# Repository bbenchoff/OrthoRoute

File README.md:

<table width="100%">
  <tr>
    <td align="center" width="300">
      
    </td>
    <td align="left">
      <h2>OrthoRoute - GPU Accelerated Autorouting for KiCad</h2>
      <p><strong>OrthoRoute is a GPU-accelerated PCB autorouter designed specifically for a narrow class of extremely large, dense, highly regular multilayer backplanes and BGA escape patterns. It uses a Manhattan lattice and the PathFinder algorithm to route designs with thousands of nets. It is not a general-purpose PCB autorouter.</strong></p>
      <p><em>Orthogonal! Non-trivial! Runs on GPUs! I live in San Francisco!</em></p>
      <p><em>Never trust the autorouter, but at least this one is fast. </em></p>
    </td>
  </tr>
</table>

> [!CAUTION]
> **OrthoRoute is not a general-purpose PCB autorouter.**
>
> OrthoRoute is designed for a narrow class of extremely large, dense, highly
> regular multilayer backplanes and BGA escape patterns. It is useful to about
> five people on the planet, and you probably aren't one of them. For a 
> conventional PCB, use something else.
>
> In *[PCBWorld: A Benchmark Environment for Engine-Grounded PCB Design
> Automation](https://arxiv.org/abs/2607.05915)*, Song et al. benchmarked
> OrthoRoute against Freerouting, KiCadRoutingTools, and several learned routing
> agents on synthetic and open-source PCB datasets.[^pcbworld]
>
> * On the synthetic D2 dataset, OrthoRoute achieved a **1% clean-pass rate**
>   and **30% routability**.
> * On D3-A, a set of 99 open-source boards, it achieved a **2% clean-pass
>   rate** and **51% routability**.
> * Freerouting and KiCadRoutingTools performed dramatically better on both
>   datasets.
>
> The benchmark used small, ordinary boards and OrthoRoute's upstream defaults;
> it did not test OrthoRoute's intended thousands-net backplane workload. It
> nevertheless demonstrates that OrthoRoute is a terrible default choice for
> ordinary PCB autorouting.

[^pcbworld]: Hyungseok Song et al., “[PCBWorld: A Benchmark Environment for
Engine-Grounded PCB Design Automation](https://arxiv.org/abs/2607.05915),”
*arXiv preprint* arXiv:2607.05915, 2026, Table 3 and Appendix K.5.

A much more comprehensive explanation of the _WHY_ and _HOW_ of this repository is available on the [build log for this project](https://bbenchoff.github.io/pages/OrthoRoute.html).

## Videos

<table>
  <tr>
    <td align="center" width="33%">
      <a href="https://www.youtube.com/watch?v=KXxxNQPTagA">
        
        <br/>
        <b>OrthoRoute Overview</b>
      </a>
    </td>
    <td align="center" width="33%">
      <a href="https://www.youtube.com/watch?v=P8Wsej71XAQ">
        
        <br/>
        <b>Algorithm Demonstration</b>
      </a>
    </td>
    <td align="center" width="33%">
      <a href="https://www.youtube.com/watch?v=j_XJNxEXXkQ">
        
        <br/>
        <b>PathFinder Net Tour</b>
      </a>
    </td>
  </tr>
</table>

## What Is Orthoroute?

OrthoRoute is a KiCad autorouter for _exceptionally large_ or _very complex_ backplane designs and BGA escape patterns. The simplified idea behind this algorithm is, "put all your parts on the top layer, and on layers below that, create a grid of traces. Only horizontal traces on layer 1, only vertical traces on layer 2, and continue like that for all the other layers. Route through this 'Manhattan grid' of traces with blind and buried vias".

The algorithm used for this autorouter is [PathFinder: a negotiation-based performance-driven router for FPGAs](https://dl.acm.org/doi/10.1145/201310.201328). My implementation of PathFinder treats the PCB as a graph: nodes are intersections on an x–y grid where vias can go, and edges are the segments between intersections where copper traces can run. Each edge and node is treated as a shared resource.

PathFinder is iterative. In the first iteration, all nets (airwires) are routed _greedily_, without accounting for overuse of nodes or edges. Subsequent iterations account for congestion, increasing the “cost” of overused edges and ripping up the worst offenders to re-route them. Over time, the algorithm _converges_ to a PCB layout where no edge or node is over-subscribed by multiple nets.

With this architecture -- the PathFinder algorithm on a very large graph, within the same order of magnitude of the largest FPGAs -- it makes sense to run the algorithm with GPU acceleration. There are a few factors that went into this decision:

1. Everyone who's routing giant backplanes probably has a gaming PC. Or you can rent a GPU from whatever company is advertising on MUNI bus stops this month.
2. The PathFinder algorithm requires hundreds of billions of calculations for every iteration, making single-core CPU computation glacially slow. 
3. With CUDA, I can implement a SSSP (parallel Dijkstra) to find a path through a weighted graph very fast. 

Note this is _not_ a fully parallel autorouter; in OrthoRoute, nets are still routed in sequence on a shared congestion map. The parallelism lives inside the shortest-path search: a CUDA SSSP (“parallel Dijkstra”) kernel makes each individual net’s pathfinding fast, but it doesn’t route many nets simultaneously.

## Features

- KiCad Integration: Built as a native KiCad plugin using the IPC API
- GPU-Accelerated Routing: Uses CUDA/CuPy or Apple Silicon/Metal
- Manhattan Routing: Specialized for orthogonal routing patterns (horizontal/vertical layer pairs)
- Real-time Visualization: Interactive 2D board view with zoom, pan, and layer controls
- Checkpoint system for instant resume after crashes (experimental)
- Headless (Cloud) Routing: Rent an A100 GPU in some datacenter

## Screenshots

### Main Interface

<div align="center">
  
  <br>
  <em>OrthoRoute plugin showing a successful Manhattan route</em>
</div>

<div align="center">
  
  <br>
  <em>A view of what the 'Manhattan Lattice' looks like in KiCad</em>
</div>

<div align="center">
  
  <br>
  <em>OrthoRoute plugin showing a successful Manhattan route</em>
</div>

## Quick Start

### Prerequisites
- **KiCad 10.0+** with the API server enabled under Preferences → Plugins
- An NVIDIA CUDA 12 GPU on Windows/Linux, or Apple Silicon on macOS
- Enough accelerator memory for the board and routing grid

### Installation Methods

#### Install the KiCad package

1. Download
   [`OrthoRoute-1.0.0-KiCad-PCM.zip`](https://github.com/bbenchoff/OrthoRoute/releases/download/v1.0.0/OrthoRoute-1.0.0-KiCad-PCM.zip),
   or build it from source using the instructions below.
2. In KiCad 10, open **Plugin and Content Manager** and choose
   **Install from File...**.
3. Select the OrthoRoute PCM ZIP.
4. Enable the API server under **Preferences > Plugins**.
5. Restart PCB Editor and allow several minutes for KiCad to create
   OrthoRoute's isolated Python environment and install its dependencies.
6. Open a board and launch **OrthoRoute** from
   **Tools > External Plugins**.

#### Build the package from source

Clone the repository and run the package builder:

```bash
git clone https://github.com/bbenchoff/OrthoRoute.git
cd OrthoRoute
python build.py
```

The builder creates:

- `build/OrthoRoute-1.0.0-KiCad-PCM.zip` for KiCad 10's
  **Install from File...** command
- `build/OrthoRoute-1.0.0-KiCad-IPC.zip` for manual native-plugin installation

Developers can build and deploy directly into their newest local KiCad
installation:

```bash
python build.py --deploy
```

Use `python build.py --deploy --kicad-version 10.0` to target KiCad 10
explicitly. Standalone development remains available with `python main.py`.

## Will it work with _my_ GPU?

As long as you have an NVIDIA card or Apple Silicon, yeah, probably. If it doesn't run on your card/computer, [open a new issue](https://github.com/bbenchoff/OrthoRoute/issues).

**Important distinction:**
- **VRAM usage** is determined by board dimensions, layers, and grid pitch (not net count)
- **Routing time** is determined by number of nets
- Example: 500 nets vs 8,000 nets on the same 200×200mm 20-layer board uses the **same VRAM** but takes **16x longer** to route

**If you get "Out of Memory" errors:** Rent a GPU with more VRAM or use `--cpu-only` mode (slower but no memory limit).

## Usage

### GUI Mode (Recommended)
1. **Open your PCB** in KiCad 10.0+ with the API server enabled
2. **Launch OrthoRoute** from the PCB Editor toolbar
3. **Route your nets** - OrthoRoute will automatically:
   - Extract board data via KiCad IPC API
   - Build 3D routing lattice (multi-layer Manhattan routing)
   - Map pads to routing graph
   - Route nets using GPU-accelerated PathFinder
5. **Monitor progress** in the interactive PCB viewer
6. **Review results** - tracks and vias are automatically added to KiCad

### Standalone Mode (For Testing)
```bash
# Built-in acceptance test (synthetic board routing)
python main.py --test-manhattan

# Run regression tests
pytest tests/                                    # All tests (unit + regression)
pytest tests/regression/test_backplane.py -v    # Full regression suite (63 tests)
pytest tests/unit/ -v                           # Unit tests only (167 tests)
```

**Note:** CLI mode (`python main.py cli board.kicad_pcb`) is designed for development/debugging and requires KiCad to be running with the board open in PCB Editor.

### Cloud (Headless, Kicad-less) Mode
Headless mode is designed for instances when you would like to route a board, but it won't fit in your GPU. This mode is actually several functions that allow for running a routing algorithm _without KiCad_.

<div align="center">
  
  <br>
  <em>Cloud routing workflow for running OrthoRoute on remote GPU instances</em>
  <br>
</div>

The workflow is three steps. First, export the PCB from the OrthoRoute plugin
1. Load a PCB in KiCad
2. Run the OrthoRoute plugin
3. Select `File -> Export PCB...` from the top menu
4. Save this file (with `.ORP` extension) to disk

Second, run OrthoRoute using the saved `.ORP` file:
  ```bash
  python main.py headless <your-board>.ORP

    Optional parameters:
  python main.py headless <board>.ORP --max-iterations 200    # Set max iterations (default: 200)
  python main.py headless <board>.ORP -o custom.ORS           # Specify output filename
  python main.py headless <board>.ORP --use-gpu               # Force GPU mode
  python main.py headless <board>.ORP --cpu-only              # Force CPU-only mode
  ```

Third, import the routing solution back into KiCad:
1. In the OrthoRoute plugin, select `File -> Import Solution...` (or press Ctrl+I)
2. Select the generated `.ORS` file
3. Review the routing in the preview window
4. Click "Apply to KiCad" to commit the traces and vias to your PCB

Typical use case: Cloud GPU routing

Upload your .ORP file to a cloud GPU instance (Vast.ai, RunPod, etc.), run the routing there, then download the .ORS file back to your local machine for import. This allows routing large boards on powerful GPUs with more memory. Details on the file format are available [in the docs](docs/ORP_ORS_file_formats.md)

### Debug Mode & Logging

By default OrthoRoute runs in **normal mode** — minimal log output, no iteration screenshots:

| Behaviour | Normal mode (default) | Debug mode (`ORTHO_DEBUG=1`) |
|---|---|---|
| Log file level | `WARNING` only (~66 milestone lines/run) | `DEBUG` (full detail) |
| Iteration screenshots | Disabled | Saved to `debug_output/` at 8× resolution |
| Screenshot frequency | — | Every N iterations (`ORTHO_SCREENSHOT_FREQ`) |
| Screenshot scale | — | 8× default (`ORTHO_SCREENSHOT_SCALE`) |

**Enable debug mode before launching KiCad (PowerShell):**
```powershell
$env:ORTHO_DEBUG = '1'
start kicad          # or however you launch KiCad
```

**Fine-tune screenshot output:**
```powershell
$env:ORTHO_DEBUG             = '1'   # master switch
$env:ORTHO_SCREENSHOT_FREQ   = '5'   # screenshot every 5 iterations
$env:ORTHO_SCREENSHOT_SCALE  = '4'   # 4× resolution instead of 8×
```

**Disable again:**
```powershell
Remove-Item Env:ORTHO_DEBUG
```

Log files are always written to `<plugin_dir>/logs/` regardless of mode.

##  Contributing

Please see [`docs/contributing.md`](docs/contributing.md) for guidelines.

If something's not working or you just don't like it, first please complain. Complaining about free stuff will actually force me to fix it. I would especially like to hear from you if you think it sucks.

## License

This project is licensed under the MIT License - see the [LICENSE](LICENSE) file for details.

## Acknowledgments

- KiCad development team for the excellent IPC API
- NVIDIA for CUDA/CuPy GPU acceleration support
- The open-source PCB design community

- **Issues**: [GitHub Issues](https://github.com/bbenchoff/OrthoRoute/issues)
- **Discussions**: [GitHub Discussions](https://github.com/bbenchoff/OrthoRoute/discussions)
- **Documentation**: [Project Wiki](https://github.com/bbenchoff/OrthoRoute/wiki)

---

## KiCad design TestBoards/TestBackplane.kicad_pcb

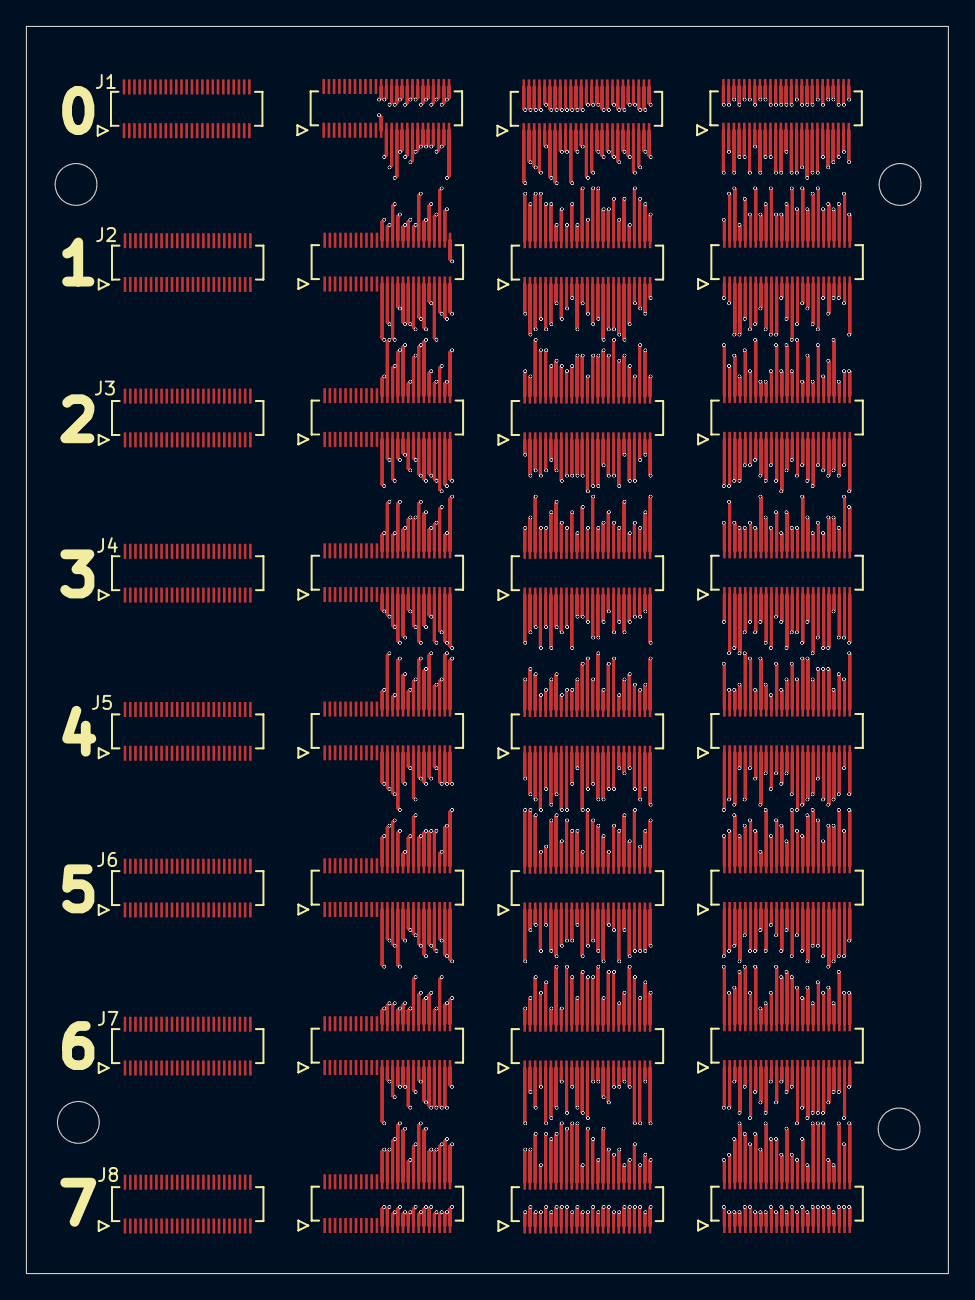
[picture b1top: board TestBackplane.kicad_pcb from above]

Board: 18 copper layers, 70.6 x 95.5 mm, 12 parts (0 on the bottom side), 512 nets.

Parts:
H1, H2, H3, H4: MountingHole; MountingHole_3.2mm_M3
J1, J2, J3, J4, J5, J6, J7, J8: BackplaneConn; Backplane-200-renumbered

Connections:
B00B01_000: J1.1, J2.1
B00B01_001: J1.5, J2.2
B00B01_002: J1.9, J2.3
B00B01_003: J1.13, J2.4
B00B01_004: J1.17, J2.5
B00B01_005: J1.21, J2.6
B00B01_006: J1.25, J2.7
B00B01_007: J1.29, J2.8
B00B01_008: J1.33, J2.9
B00B01_009: J1.37, J2.10
B00B01_010: J1.41, J2.11
B00B01_011: J1.45, J2.12
B00B01_012: J1.49, J2.13
B00B01_013: J1.53, J2.14
B00B01_014: J1.57, J2.15
B00B01_015: J1.61, J2.16
B00B02_000: J1.2, J3.1
B00B02_001: J1.6, J3.2
B00B02_002: J1.10, J3.3
B00B02_003: J1.14, J3.4
B00B02_004: J1.18, J3.5
B00B02_005: J1.22, J3.6
B00B02_006: J1.26, J3.7
B00B02_007: J1.30, J3.8
B00B02_008: J1.34, J3.9
B00B02_009: J1.38, J3.10
B00B02_010: J1.42, J3.11
B00B02_011: J1.46, J3.12
B00B02_012: J1.50, J3.13
B00B02_013: J1.54, J3.14
B00B02_014: J1.58, J3.15
B00B02_015: J1.62, J3.16
B00B04_000: J1.3, J5.1
B00B04_001: J1.7, J5.2
B00B04_002: J1.11, J5.3
B00B04_003: J1.15, J5.4
B00B04_004: J1.19, J5.5
B00B04_005: J1.23, J5.6
B00B04_006: J1.27, J5.7
B00B04_007: J1.31, J5.8
B00B04_008: J1.35, J5.9
B00B04_009: J1.39, J5.10
B00B04_010: J1.43, J5.11
B00B04_011: J1.47, J5.12
B00B04_012: J1.51, J5.13
B00B04_013: J1.55, J5.14
B00B04_014: J1.59, J5.15
B00B04_015: J1.63, J5.16
B00B08_000: J1.4, J1.65
B00B08_001: J1.8, J1.66
B00B08_002: J1.12, J1.67
B00B08_003: J1.16, J1.68
B00B08_004: J1.20, J1.69
B00B08_005: J1.24, J1.70
B00B08_006: J1.28, J1.71
B00B08_007: J1.32, J1.72
B00B08_008: J1.36, J1.73
B00B08_009: J1.40, J1.74
B00B08_010: J1.44, J1.75
B00B08_011: J1.48, J1.76
B00B08_012: J1.52, J1.77
B00B08_013: J1.56, J1.78
B00B08_014: J1.60, J1.79
B00B08_015: J1.64, J1.80
B01B03_000: J2.17, J4.1
B01B03_001: J2.20, J4.2
B01B03_002: J2.23, J4.3
B01B03_003: J2.26, J4.4
B01B03_004: J2.29, J4.5
B01B03_005: J2.32, J4.6
B01B03_006: J2.35, J4.7
B01B03_007: J2.38, J4.8
B01B03_008: J2.41, J4.9
B01B03_009: J2.44, J4.10
B01B03_010: J2.47, J4.11
B01B03_011: J2.50, J4.12
B01B03_012: J2.53, J4.13
B01B03_013: J2.56, J4.14
B01B03_014: J2.59, J4.15
B01B03_015: J2.62, J4.16
B01B05_000: J2.18, J6.1
B01B05_001: J2.21, J6.2
B01B05_002: J2.24, J6.3
B01B05_003: J2.27, J6.4
B01B05_004: J2.30, J6.5
B01B05_005: J2.33, J6.6
B01B05_006: J2.36, J6.7
B01B05_007: J2.39, J6.8
B01B05_008: J2.42, J6.9
B01B05_009: J2.45, J6.10
B01B05_010: J2.48, J6.11
B01B05_011: J2.51, J6.12
B01B05_012: J2.54, J6.13
B01B05_013: J2.57, J6.14
B01B05_014: J2.60, J6.15
B01B05_015: J2.63, J6.16
B01B09_000: J2.19, J2.65
B01B09_001: J2.22, J2.66
B01B09_002: J2.25, J2.67
B01B09_003: J2.28, J2.68
B01B09_004: J2.31, J2.69
B01B09_005: J2.34, J2.70
B01B09_006: J2.37, J2.71
B01B09_007: J2.40, J2.72
B01B09_008: J2.43, J2.73
B01B09_009: J2.46, J2.74
B01B09_010: J2.49, J2.75
B01B09_011: J2.52, J2.76
B01B09_012: J2.55, J2.77
B01B09_013: J2.58, J2.78
B01B09_014: J2.61, J2.79
B01B09_015: J2.64, J2.80
B02B03_000: J3.17, J4.17
B02B03_001: J3.20, J4.18
B02B03_002: J3.23, J4.19
B02B03_003: J3.26, J4.20
B02B03_004: J3.29, J4.21
B02B03_005: J3.32, J4.22
B02B03_006: J3.35, J4.23
B02B03_007: J3.38, J4.24
B02B03_008: J3.41, J4.25
B02B03_009: J3.44, J4.26
B02B03_010: J3.47, J4.27
B02B03_011: J3.50, J4.28
B02B03_012: J3.53, J4.29
B02B03_013: J3.56, J4.30
B02B03_014: J3.59, J4.31
B02B03_015: J3.62, J4.32
B02B06_000: J3.18, J7.1
B02B06_001: J3.21, J7.2
B02B06_002: J3.24, J7.3
B02B06_003: J3.27, J7.4
B02B06_004: J3.30, J7.5
B02B06_005: J3.33, J7.6
B02B06_006: J3.36, J7.7
B02B06_007: J3.39, J7.8
B02B06_008: J3.42, J7.9
B02B06_009: J3.45, J7.10
B02B06_010: J3.48, J7.11
B02B06_011: J3.51, J7.12
B02B06_012: J3.54, J7.13
B02B06_013: J3.57, J7.14
B02B06_014: J3.60, J7.15
B02B06_015: J3.63, J7.16
B02B10_000: J3.19, J3.65
B02B10_001: J3.22, J3.66
B02B10_002: J3.25, J3.67
B02B10_003: J3.28, J3.68
B02B10_004: J3.31, J3.69
B02B10_005: J3.34, J3.70
B02B10_006: J3.37, J3.71
B02B10_007: J3.40, J3.72
B02B10_008: J3.43, J3.73
B02B10_009: J3.46, J3.74
B02B10_010: J3.49, J3.75
B02B10_011: J3.52, J3.76
B02B10_012: J3.55, J3.77
B02B10_013: J3.58, J3.78
B02B10_014: J3.61, J3.79
B02B10_015: J3.64, J3.80
B03B07_000: J4.33, J8.1
B03B07_001: J4.35, J8.2
B03B07_002: J4.37, J8.3
B03B07_003: J4.39, J8.4
B03B07_004: J4.41, J8.5
B03B07_005: J4.43, J8.6
B03B07_006: J4.45, J8.7
B03B07_007: J4.47, J8.8
B03B07_008: J4.49, J8.9
B03B07_009: J4.51, J8.10
B03B07_010: J4.53, J8.11
B03B07_011: J4.55, J8.12
B03B07_012: J4.57, J8.13
B03B07_013: J4.59, J8.14
B03B07_014: J4.61, J8.15
B03B07_015: J4.63, J8.16
B03B11_000: J4.34, J4.65
B03B11_001: J4.36, J4.66
B03B11_002: J4.38, J4.67
B03B11_003: J4.40, J4.68
B03B11_004: J4.42, J4.69
B03B11_005: J4.44, J4.70
B03B11_006: J4.46, J4.71
B03B11_007: J4.48, J4.72
B03B11_008: J4.50, J4.73
B03B11_009: J4.52, J4.74
B03B11_010: J4.54, J4.75
B03B11_011: J4.56, J4.76
B03B11_012: J4.58, J4.77
B03B11_013: J4.60, J4.78
B03B11_014: J4.62, J4.79
B03B11_015: J4.64, J4.80
B04B05_000: J5.17, J6.17
B04B05_001: J5.20, J6.18
B04B05_002: J5.23, J6.19
B04B05_003: J5.26, J6.20
B04B05_004: J5.29, J6.21
B04B05_005: J5.32, J6.22
B04B05_006: J5.35, J6.23
B04B05_007: J5.38, J6.24
B04B05_008: J5.41, J6.25
B04B05_009: J5.44, J6.26
B04B05_010: J5.47, J6.27
B04B05_011: J5.50, J6.28
B04B05_012: J5.53, J6.29
B04B05_013: J5.56, J6.30
B04B05_014: J5.59, J6.31
B04B05_015: J5.62, J6.32
B04B06_000: J5.18, J7.17
B04B06_001: J5.21, J7.18
B04B06_002: J5.24, J7.19
B04B06_003: J5.27, J7.20
B04B06_004: J5.30, J7.21
B04B06_005: J5.33, J7.22
B04B06_006: J5.36, J7.23
B04B06_007: J5.39, J7.24
B04B06_008: J5.42, J7.25
B04B06_009: J5.45, J7.26
B04B06_010: J5.48, J7.27
B04B06_011: J5.51, J7.28
B04B06_012: J5.54, J7.29
B04B06_013: J5.57, J7.30
B04B06_014: J5.60, J7.31
B04B06_015: J5.63, J7.32
B04B12_000: J5.19, J5.65
B04B12_001: J5.22, J5.66
B04B12_002: J5.25, J5.67
B04B12_003: J5.28, J5.68
B04B12_004: J5.31, J5.69
B04B12_005: J5.34, J5.70
B04B12_006: J5.37, J5.71
B04B12_007: J5.40, J5.72
B04B12_008: J5.43, J5.73
B04B12_009: J5.46, J5.74
B04B12_010: J5.49, J5.75
B04B12_011: J5.52, J5.76
B04B12_012: J5.55, J5.77
B04B12_013: J5.58, J5.78
B04B12_014: J5.61, J5.79
B04B12_015: J5.64, J5.80
B05B07_000: J6.33, J8.17
B05B07_001: J6.35, J8.18
B05B07_002: J6.37, J8.19
B05B07_003: J6.39, J8.20
B05B07_004: J6.41, J8.21
B05B07_005: J6.43, J8.22
B05B07_006: J6.45, J8.23
B05B07_007: J6.47, J8.24
B05B07_008: J6.49, J8.25
B05B07_009: J6.51, J8.26
B05B07_010: J6.53, J8.27
B05B07_011: J6.55, J8.28
B05B07_012: J6.57, J8.29
B05B07_013: J6.59, J8.30
B05B07_014: J6.61, J8.31
B05B07_015: J6.63, J8.32
B05B13_000: J6.34, J6.65
B05B13_001: J6.36, J6.66
B05B13_002: J6.38, J6.67
B05B13_003: J6.40, J6.68
B05B13_004: J6.42, J6.69
B05B13_005: J6.44, J6.70
B05B13_006: J6.46, J6.71
B05B13_007: J6.48, J6.72
B05B13_008: J6.50, J6.73
B05B13_009: J6.52, J6.74
B05B13_010: J6.54, J6.75
B05B13_011: J6.56, J6.76
B05B13_012: J6.58, J6.77
B05B13_013: J6.60, J6.78
B05B13_014: J6.62, J6.79
B05B13_015: J6.64, J6.80
B06B07_000: J7.33, J8.33
B06B07_001: J7.35, J8.34
B06B07_002: J7.37, J8.35
B06B07_003: J7.39, J8.36
B06B07_004: J7.41, J8.37
B06B07_005: J7.43, J8.38
B06B07_006: J7.45, J8.39
B06B07_007: J7.47, J8.40
B06B07_008: J7.49, J8.41
B06B07_009: J7.51, J8.42
B06B07_010: J7.53, J8.43
B06B07_011: J7.55, J8.44
B06B07_012: J7.57, J8.45
B06B07_013: J7.59, J8.46
B06B07_014: J7.61, J8.47
B06B07_015: J7.63, J8.48
B06B14_000: J7.34, J7.65
B06B14_001: J7.36, J7.66
B06B14_002: J7.38, J7.67
B06B14_003: J7.40, J7.68
B06B14_004: J7.42, J7.69
B06B14_005: J7.44, J7.70
B06B14_006: J7.46, J7.71
B06B14_007: J7.48, J7.72
B06B14_008: J7.50, J7.73
B06B14_009: J7.52, J7.74
B06B14_010: J7.54, J7.75
B06B14_011: J7.56, J7.76
B06B14_012: J7.58, J7.77
B06B14_013: J7.60, J7.78
B06B14_014: J7.62, J7.79
B06B14_015: J7.64, J7.80
B07B15_000: J8.49, J8.65
B07B15_001: J8.50, J8.66
B07B15_002: J8.51, J8.67
B07B15_003: J8.52, J8.68
B07B15_004: J8.53, J8.69
B07B15_005: J8.54, J8.70
B07B15_006: J8.55, J8.71
B07B15_007: J8.56, J8.72
B07B15_008: J8.57, J8.73
B07B15_009: J8.58, J8.74
B07B15_010: J8.59, J8.75
B07B15_011: J8.60, J8.76
B07B15_012: J8.61, J8.77
B07B15_013: J8.62, J8.78
B07B15_014: J8.63, J8.79
B07B15_015: J8.64, J8.80
B08B09_000: J1.81, J2.81
B08B09_001: J1.84, J2.82
B08B09_002: J1.87, J2.83
B08B09_003: J1.90, J2.84
B08B09_004: J1.93, J2.85
B08B09_005: J1.96, J2.86
B08B09_006: J1.99, J2.87
B08B09_007: J1.102, J2.88
B08B09_008: J1.105, J2.89
B08B09_009: J1.108, J2.90
B08B09_010: J1.111, J2.91
B08B09_011: J1.114, J2.92
B08B09_012: J1.117, J2.93
B08B09_013: J1.120, J2.94
B08B09_014: J1.123, J2.95
B08B09_015: J1.126, J2.96
B08B10_000: J1.82, J3.81
B08B10_001: J1.85, J3.82
B08B10_002: J1.88, J3.83
B08B10_003: J1.91, J3.84
B08B10_004: J1.94, J3.85
B08B10_005: J1.97, J3.86
B08B10_006: J1.100, J3.87
B08B10_007: J1.103, J3.88
B08B10_008: J1.106, J3.89
B08B10_009: J1.109, J3.90
B08B10_010: J1.112, J3.91
B08B10_011: J1.115, J3.92
B08B10_012: J1.118, J3.93
B08B10_013: J1.121, J3.94
B08B10_014: J1.124, J3.95
B08B10_015: J1.127, J3.96
B08B12_000: J1.83, J5.81
B08B12_001: J1.86, J5.82
B08B12_002: J1.89, J5.83
B08B12_003: J1.92, J5.84
B08B12_004: J1.95, J5.85
B08B12_005: J1.98, J5.86
B08B12_006: J1.101, J5.87
B08B12_007: J1.104, J5.88
B08B12_008: J1.107, J5.89
B08B12_009: J1.110, J5.90
B08B12_010: J1.113, J5.91
B08B12_011: J1.116, J5.92
B08B12_012: J1.119, J5.93
B08B12_013: J1.122, J5.94
B08B12_014: J1.125, J5.95
B08B12_015: J1.128, J5.96
B09B11_000: J2.97, J4.81
B09B11_001: J2.99, J4.82
B09B11_002: J2.101, J4.83
B09B11_003: J2.103, J4.84
B09B11_004: J2.105, J4.85
B09B11_005: J2.107, J4.86
B09B11_006: J2.109, J4.87
B09B11_007: J2.111, J4.88
B09B11_008: J2.113, J4.89
B09B11_009: J2.115, J4.90
B09B11_010: J2.117, J4.91
B09B11_011: J2.119, J4.92
B09B11_012: J2.121, J4.93
B09B11_013: J2.123, J4.94
B09B11_014: J2.125, J4.95
B09B11_015: J2.127, J4.96
B09B13_000: J2.98, J6.81
B09B13_001: J2.100, J6.82
B09B13_002: J2.102, J6.83
B09B13_003: J2.104, J6.84
B09B13_004: J2.106, J6.85
B09B13_005: J2.108, J6.86
B09B13_006: J2.110, J6.87
B09B13_007: J2.112, J6.88
B09B13_008: J2.114, J6.89
B09B13_009: J2.116, J6.90
B09B13_010: J2.118, J6.91
B09B13_011: J2.120, J6.92
B09B13_012: J2.122, J6.93
B09B13_013: J2.124, J6.94
B09B13_014: J2.126, J6.95
B09B13_015: J2.128, J6.96
B10B11_000: J3.97, J4.97
B10B11_001: J3.99, J4.98
B10B11_002: J3.101, J4.99
B10B11_003: J3.103, J4.100
B10B11_004: J3.105, J4.101
B10B11_005: J3.107, J4.102
B10B11_006: J3.109, J4.103
B10B11_007: J3.111, J4.104
B10B11_008: J3.113, J4.105
B10B11_009: J3.115, J4.106
B10B11_010: J3.117, J4.107
B10B11_011: J3.119, J4.108
B10B11_012: J3.121, J4.109
B10B11_013: J3.123, J4.110
B10B11_014: J3.125, J4.111
B10B11_015: J3.127, J4.112
B10B14_000: J3.98, J7.81
B10B14_001: J3.100, J7.82
B10B14_002: J3.102, J7.83
B10B14_003: J3.104, J7.84
B10B14_004: J3.106, J7.85
B10B14_005: J3.108, J7.86
B10B14_006: J3.110, J7.87
B10B14_007: J3.112, J7.88
B10B14_008: J3.114, J7.89
B10B14_009: J3.116, J7.90
B10B14_010: J3.118, J7.91
B10B14_011: J3.120, J7.92
B10B14_012: J3.122, J7.93
B10B14_013: J3.124, J7.94
B10B14_014: J3.126, J7.95
B10B14_015: J3.128, J7.96
B11B15_000: J4.113, J8.81
B11B15_001: J4.114, J8.82
B11B15_002: J4.115, J8.83
B11B15_003: J4.116, J8.84
B11B15_004: J4.117, J8.85
B11B15_005: J4.118, J8.86
B11B15_006: J4.119, J8.87
B11B15_007: J4.120, J8.88
B11B15_008: J4.121, J8.89
B11B15_009: J4.122, J8.90
B11B15_010: J4.123, J8.91
B11B15_011: J4.124, J8.92
B11B15_012: J4.125, J8.93
B11B15_013: J4.126, J8.94
B11B15_014: J4.127, J8.95
B11B15_015: J4.128, J8.96
B12B13_000: J5.97, J6.97
B12B13_001: J5.99, J6.98
B12B13_002: J5.101, J6.99
B12B13_003: J5.103, J6.100
B12B13_004: J5.105, J6.101
B12B13_005: J5.107, J6.102
B12B13_006: J5.109, J6.103
B12B13_007: J5.111, J6.104
B12B13_008: J5.113, J6.105
B12B13_009: J5.115, J6.106
B12B13_010: J5.117, J6.107
B12B13_011: J5.119, J6.108
B12B13_012: J5.121, J6.109
B12B13_013: J5.123, J6.110
B12B13_014: J5.125, J6.111
B12B13_015: J5.127, J6.112
B12B14_000: J5.98, J7.97
B12B14_001: J5.100, J7.98
B12B14_002: J5.102, J7.99
B12B14_003: J5.104, J7.100
B12B14_004: J5.106, J7.101
B12B14_005: J5.108, J7.102
B12B14_006: J5.110, J7.103
B12B14_007: J5.112, J7.104
B12B14_008: J5.114, J7.105
B12B14_009: J5.116, J7.106
B12B14_010: J5.118, J7.107
B12B14_011: J5.120, J7.108
B12B14_012: J5.122, J7.109
B12B14_013: J5.124, J7.110
B12B14_014: J5.126, J7.111
B12B14_015: J5.128, J7.112
B13B15_000: J6.113, J8.97
B13B15_001: J6.114, J8.98
B13B15_002: J6.115, J8.99
B13B15_003: J6.116, J8.100
B13B15_004: J6.117, J8.101
B13B15_005: J6.118, J8.102
B13B15_006: J6.119, J8.103
B13B15_007: J6.120, J8.104
B13B15_008: J6.121, J8.105
B13B15_009: J6.122, J8.106
B13B15_010: J6.123, J8.107
B13B15_011: J6.124, J8.108
B13B15_012: J6.125, J8.109
B13B15_013: J6.126, J8.110
B13B15_014: J6.127, J8.111
B13B15_015: J6.128, J8.112
B14B15_000: J7.113, J8.113
B14B15_001: J7.114, J8.114
B14B15_002: J7.115, J8.115
B14B15_003: J7.116, J8.116
B14B15_004: J7.117, J8.117
B14B15_005: J7.118, J8.118
B14B15_006: J7.119, J8.119
B14B15_007: J7.120, J8.120
B14B15_008: J7.121, J8.121
B14B15_009: J7.122, J8.122
B14B15_010: J7.123, J8.123
B14B15_011: J7.124, J8.124
B14B15_012: J7.125, J8.125
B14B15_013: J7.126, J8.126
B14B15_014: J7.127, J8.127
B14B15_015: J7.128, J8.128

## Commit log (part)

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2025-11-16 Fail-fast GPU mode: skip CPU fallback, exclude failing nets after 5 attempts, reduce diagnostic overhead
2025-11-16 GPU-vectorized layer diagnostics + fail-fast mode + logging
2025-11-16 Vectorized conflict detection
2025-11-16 added versioning in logging
2025-11-18 added pics
2025-11-20 derive max iterations is actually real
2025-11-20 fix OpenGL
2025-12-02 found IPC API incompatability with Content and plugin manager; updated instructions.
2025-12-16 Fixed error
2026-01-31 Add cross-platform GPU support with NumPy/MLX fallback for Apple Silicon
    This change enables OrthoRoute to run on systems without NVIDIA CUDA,
    including Apple Silicon Macs, by providing:
    - MLX provider for Apple Silicon GPU acceleration via Metal
    - NumPy-based fallback implementations of CUDA kernels
    - Compute backend abstraction layer for unified array operations
    - CuPy compatibility layer for gradual migration
2026-01-31 Remove remaining inline cupy imports for complete Apple Silicon support
    Fixed all remaining inline `import cupy as cp` statements in mixin files
    that were causing potential issues. These files now use the module-level
    cp import from cupy_compat.
    Files fixed:
    - lattice_builder_mixin.py (line 884)
    - graph_builder_mixin.py (lines 44, 54, 65, 432)
2026-01-31 Add mlx to requirements.txt for Apple Silicon support
    Uncommented mlx dependency so it's properly listed as an optional
    GPU acceleration package for Apple Silicon users.
    https://claude.ai/code/session_01SpCN9cjbyudkcNYJAB59XL
2026-04-01 Fix KiCad SWIG plugin: cross-platform launch, IPC auto-discovery, Qt plugin path
    - Add swig_init.py: SWIG ActionPlugin that registers toolbar button and
    launches main.py as subprocess in plugin mode (kipy auto-discovers IPC
    socket, no KICAD_API_SOCKET env var needed)
    - Cross-platform support: per-platform Python exe, kicad bin dir,
    3rdparty site-packages detection (Windows/Linux/macOS)
    - Set QT_PLUGIN_PATH so PyQt6 finds platform plugins in subprocess env
2026-04-01 Fix track/via extraction and board viewer rendering
    - rich_kicad_interface.py: correct IPC API attribute access for tracks/vias,
    nm->mm conversion, BoardLayer enum name mapping (BL_F_Cu -> F.Cu),
    new _extract_vias() method
    - main_window.py: normalize BL_* layer names in paint loop,
    RoundCap/RoundJoin pen for track rendering
    - .gitignore: exclude copy_to_kicad.ps1 (local dev tool only)
2026-04-01 Add copper zone extraction and rendering
    - rich_kicad_interface.py: implement _extract_zones() using KiCad IPC API
    board.get_zones(); skips rule areas (logged by name); extracts outline
    and filled_polygons per layer with nm->mm conversion and BL_* layer name
    mapping; logs skip reasons for rule area zones
    - main_window.py: add _draw_zones() with semi-transparent layer-colored fills
    respecting visible_layers checkbox; wired into paint loop under show_zones toggle
2026-04-01 fix: draw keepout rule areas when show_keepouts checkbox is enabled
    Paint event now calls _draw_keepouts() when show_keepouts=True.
    New _draw_keepouts() renders each keepout outline as a dashed red
    semi-transparent polygon, respecting layer visibility.
    Previously the checkbox toggled the flag but triggered no drawing
    because no _draw_keepouts() method or call existed.
2026-04-01 feat: right-click context menu shows keepout constraints on PCB viewer
    Right-clicking inside a keepout area now shows a popup with:
    - Keepout name and affected layers
    - Per-constraint status with check/cross mark:
    No Tracks / No Vias / No Copper Fills / No Pads / No Footprints
    Uses ray-casting PIP test (_point_in_polygon) against keepout outline
    after converting screen coords -> world (mm) coords via _screen_to_world().
2026-04-01 fix: downgrade per-paint-event INFO logs to DEBUG in draw methods
    _draw_tracks, _draw_vias, _draw_zones were logging at INFO level on every
    paint event (~50ms), flooding the log with hundreds of lines per session.
    Downgraded to DEBUG: called/completed summaries, VIEWPORT DEBUG, COORD VERIFY,
    TRACK COORDS, TRACK DRAWN, TRACK LAYER FILTERED messages.
    Genuine warnings (invalid data, transform failures) remain at WARNING.
2026-04-01 fix: include orthoroute.json in build package and add to validation
    build.py --deploy and ZIP builds were missing orthoroute.json (the
    runtime config file). Added it to the extra-files copy loop and to
    the required-files validation list so a broken build fails fast.
2026-04-01 docs: update copilot-instructions with current codebase state
    - Build: corrected ZIP name, noted orthoroute.json now included and validated
    - KiCad integration: document IPC data extraction (tracks/vias/zones/keepouts),
    fix plugin folder name (underscores not dots), point to plugin logs,
    add dev-sync workflow (copy_to_kicad.ps1)
    - Key files table: add rich_kicad_interface, main_window, board.py
    - Routing: document _apply_keepout_obstacles() keepout enforcement
2026-04-03 perf: reclassify cuda_dijkstra.py logging -- 210 INFO->DEBUG, document persistent kernel fix
    - All 210 logger.info() calls converted to logger.debug()
    - [GPU-SEEDS] Path found in X iterations promoted to WARNING (key timing metric)
    - Result: log size 861MB -> ~10-20MB per run
    - Document why _enable_persistent_kernel = False:
    persistent kernel lacks allowed_bitmap param (owner-aware node filtering)
    needed to prevent routing through other nets' pad nodes
2026-04-03 perf: enable persistent CUDA kernel -- 2x speedup (48min -> 25min)
    - Add allowed_bitmap (uint32*), bitmap_words, use_bitmap params to
    persistent_sssp_kernel PTX -- owner-aware node filtering now works
    - IN_BITMAP check in inner loop matches wavefront_expand_all kernel
    - launch_persistent_kernel() updated to accept/pass bitmap params
    - _enable_persistent_kernel = True (was False since v1)
    - Bump _persistent_kernel_version to 3 (forces recompile)
2026-04-03 docs: update perf docs -- persistent kernel results + next bottleneck
    - Run time: 47.9min -> 25min (2x speedup, 70 iters, 512/512 converged)
    - New bottleneck: Python bitmap construction ~50ms/net (65% of per-net)
    int(seed) loop causes ~100 GPU->CPU syncs before kernel launch
    Fix: cp.scatter_add vectorized bitmap set (one kernel call)
    Expected gain: 25min -> ~8-10min (3-4x additional speedup)
    - Mark MULTI-LAUNCH overhead as DONE in priority table
2026-04-03 perf: bitmap GPU-resident + vectorized owner bitmap build (no net speedup)
    - cuda_dijkstra.py: skip cp.asarray() if allowed_bitmap already CuPy
    - cuda_dijkstra.py: fix cupyx.scatter_add bitmap OR corruption (build
    zero force_mask then OR into roi_bitmaps to avoid bit-flip on existing bits)
    - unified_pathfinder.py: add node_owner_gpu (CuPy mirror of node_owner)
    - unified_pathfinder.py: sync node_owner_gpu once per iter in _rebuild_node_owner
    - unified_pathfinder.py: batch-write to node_owner_gpu in _mark_via_barrel_ownership_for_path
2026-04-03 logging: ORTHO_DEBUG controls log level, screenshots, and profile_time
    - init_logging() respects ORTHO_DEBUG (was hardcoded DEBUG)
    - File log: WARNING normal / DEBUG when ORTHO_DEBUG=1
    - Console: always WARNING
    - Screenshots: disabled by default, enabled with ORTHO_DEBUG=1
    - image.save() offloaded to daemon thread (eliminates 6s inter-iter stall)
    - setup_logging(): removed duplicate component_levels loop, added dead-code note
2026-04-03 docs: add TODO for automated regression test on TestBackplane
    - Contributing.md: full spec for headless routing regression test
    - Read-only board (never modify TestBoards/TestBackplane.kicad_pcb)
    - Golden metrics: nets_routed, overuse_edges exact-or-better
    - Iterations: +-10% tolerance (non-deterministic router)
    - Timing: <=110% of golden (no performance regression)
    - Stores baseline in tests/golden_metrics.json (committed to repo)
2026-04-05 fix: 3 KiCad IPC bugs - retry on connection refused, get_open_documents arg, remove invalid .board attr
2026-04-05 fix: pipeline.py imports, rrg.py attribute names, logging to ERROR-only in normal mode
2026-04-05 docs: rewrite copilot-instructions.md; update contributing.md to reference tests/README.md
2026-04-05 chore: add agent customizations, instructions, prompts, and skills for OrthoRoute dev workflow
2026-04-05 chore: add launch_kicad_debug.ps1 debug launch script and pytest.ini
2026-04-05 test: update TestBackplane with results from successful GPU routing run (512/512 nets, 65 iters, 717s)
2026-04-05 test: add full test suite (was gitignored) + fix regression conftest log path, iter regex, GPU golden metrics
2026-04-05 test: un-ignore test_*.py inside tests/ folder; add all test files to repo
2026-04-05 test: add TestLatticeSize group + log_lattice fixture; add Apr-5 perf baseline
    - conftest.py: _parse_lattice_from_log() parses 'Lattice: NxNxN = N nodes' WARNING;
    log_lattice fixture exposes it session-wide
    - test_backplane.py: TestLatticeSize group (4 tests)
    - test_lattice_nodes: HARD FAIL if nodes != golden_board[lattice_nodes] (446,472)
    - test_lattice_layers: HARD FAIL if layers != golden_board[copper_layers] (18)
    - test_lattice_dimensions_reported: SOFT WARN on zero dims
2026-04-05 test: parse end-of-run banners from log; 25 skipped -> 0 skipped
    conftest.py - _parse_routing_result_from_log now extracts:
    - [CLEAN] All nets routed with zero overuse -> clean_zero_overuse flag
    - ROUTING COMPLETE: All N nets routed ... -> routing_complete_banner flag
    - [FINAL] Edge routing converged (N barrel) -> final_barrel_conflicts count
    - Applied N tracks and N vias to KiCad -> tracks_written / vias_written
    Convergence is now driven by hard [CLEAN]/ROUTING COMPLETE markers, not just
2026-04-05 docs: add full convergence trend table to Apr-5 baseline
    - Two-run comparison table (run1 golden ref vs run2 confirmed log)
    - PERSISTENT kernel confirmed in run2 (run_20260405_223659.log line 383)
    - Full 67-iter convergence trend: iter 1-6, 10, 20, 30, 40, 50, 60-67
    with nets_active, overuse edges, barrel conflicts, iter/total time
    - Key observations: warm-up, pres_fac cap at 64, net exclusion/retry pattern,
    barrel floor at 379, final sprint at <5s/iter
2026-04-10 Add unit tests and update optimization baseline (April 8, 2026)
    Unit tests added:
    - test_edge_accountant.py - PathFinder edge cost and congestion tracking
    - test_pathfinding.py - Dijkstra pathfinding methods (52 failing - mock issues)
    - test_real_global_grid.py - Grid coordinate conversion and validation
    - test_roi_extraction.py - Region of interest extraction (20 failing - mock issues)
    - test_rrg.py - Routing resource graph data structures
2026-04-10 feat: Add comprehensive test suite with golden result baseline
    - Add 167 unit tests (all passing)
    - Add 63 regression tests validating against golden result
    - Document golden result: April 10, 2026 (512/512 nets, zero overuse, 18.4 min)
    - Create tests/run_golden_regression.md with test documentation
    - Update golden_board.json and golden_metrics.json with validated baselines
    - Add docs/optimization/golden_result_2026-04-10.md with complete metrics
2026-04-12 Add automated optimization workflow with smoke test validation
    - Create scripts/analyze_log.py: Standalone log parser for routing metrics extraction and golden comparison
    - Create scripts/optimize_and_validate.ps1: PowerShell automation wrapper for full optimization cycle
    - Create scripts/README.md: Comprehensive documentation for automation scripts
    - Create tests/regression/smoke_metrics.json: Golden thresholds for smoke test (100 nets, 4 layers)
    - Create docs/optimization/optimization_workflow.md: Complete optimization workflow guide (800+ lines)
    - Create docs/optimization/baseline_template.md: Standardized template for future optimization baselines
2026-05-04 Include cautionary note for Orthoroute users
    Add warning about the limited usefulness of Orthoroute.
